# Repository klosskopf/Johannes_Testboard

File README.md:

# ECP5_Breakout_with_DDR2  
A LFE5U-25F68G256CFDG Breakout board with DDR2 x8 and Spi-Flash  
  
This breakout board is meant to be capable of running Linux (No idea if thats the case)  
  
### It features:  
-LFE55U-25F68G256CFDG FPGA  
-E1109AFGB 1Gbit DDR2 (desoldered from a DIMM)  
-W25Q128FV 128Mbit QSPI-Flash  
-44 GPIO Pins  

### Programming
I usually use a Altera-USB blaster as jtag cable.
That works pretty good, but I have to ignore a status bit during programmin
The programming-pinout on the board is:
|1|2||3|4|5|6|7|8|9|10|
|-|-|-|-|-|-|-|-|-|-|-|
|VIN(5V)|GND||VCC|TDO|TDI|NC|NC|TMS|GND|TCK|

This is the correct pinout for the USB ispDOWNLOAD Cable H-USBN-2A

Initial programming is done via JTAG (In my case ispDOWNLOAD Cable HW-USBN-2A))  
In future a "bootloader" should be built, to configure the Flash via serial  
  
**Do not expect this to be optimal.**  
**Do not expect this to be halfway decent.**  
**Do not expect this to work.**  
**Do not use this, but on your own risc**

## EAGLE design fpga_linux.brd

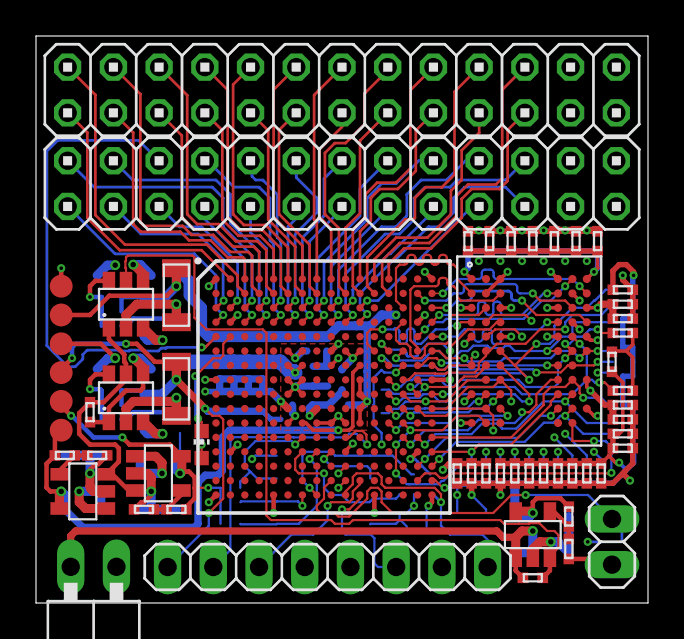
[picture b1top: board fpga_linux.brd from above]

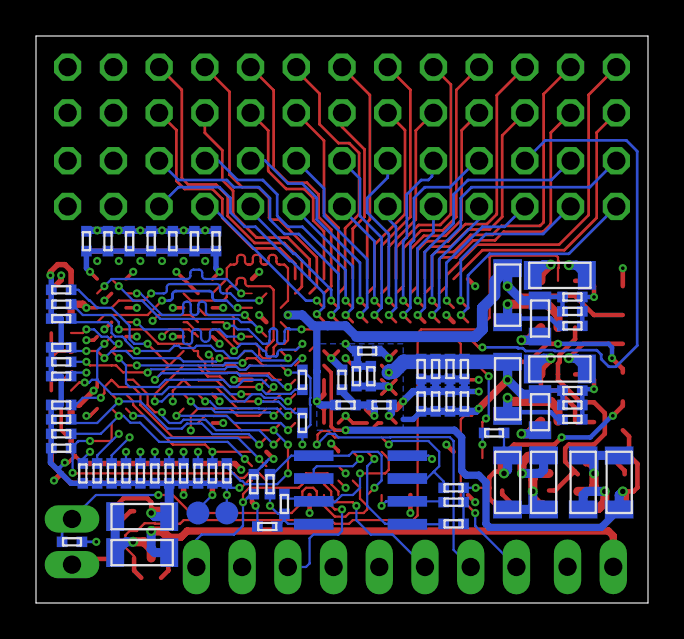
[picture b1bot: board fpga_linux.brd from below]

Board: 4 copper layers, 34.0 x 31.5 mm, 131 parts (74 on the bottom side), 110 nets.

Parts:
C1, C2, C3, C4, C5, C6, C7, C8, C9, C10, C11, C12, C13, C14, C15, C16, C17, C18, C19, C20, C21, C22, C23, C24, C25, C26, C27, C28, C29, C30, C31, C32, C33, C34, C35, C36, C37, C38, C39, C40, C41, C42, C43, C49, C50, C53, C54, C55: 0402
IC1: E1109AFGB; DDR2X8
IC2: LFE5U-25F68G256CFDG; BGA256C80P16X16_1400X1400X170
JP1: 1X08
JP2: 1X02
JP3, JP4: 2X13
LED1: CHIP-LED0603
POW:C1, POW:C2, POW:C4, POW:C5, POW:C7, POW:C8, POW:C9, POW:C11, POW:C12, POW:C13, POW:C14, POW:C15: 10u; 1206
POW:C3, POW:C10: 22p; 0402
POW:IC1, POW:IC4, POW:IC5: AP2127; SOT23-5
POW:IC2, POW:IC3: FP6373A; SOT23-6
POW:JP1: 1X02/90
POW:L1, POW:L2: 1u5; 0805
POW:R1: 56k2; 0402
POW:R2: 2k2; 0402
POW:R3, POW:R5, POW:R6: 18k; 0402
POW:R4: 38k3; 0402
POW:R7, POW:R9: 10k; 0402
POW:R10: 83k33; 0402
POW:R11, POW:R13: 100k; 0402
POW:R12: 200k; 0402
POW:TP1, POW:TP2, POW:TP3, POW:TP4, POW:TP5, POW:TP6, POW:TP7, POW:TP8: TPB1,27; B1,27
R1, R2, R8, R9, R10, R11, R12, R13, R14, R15, R16, R17, R18, R19, R20, R21, R22, R23, R24, R25, R26, R27, R28, R29, R30, R31, R32, R33: 0402
R3: 4k7; 0402
R4, R5, R6, R7: 10k; 0402
U$1: W25Q64FCSOIC8; SOIC8

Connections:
1V8: C3.2, C4.2, C5.2, C6.2, C7.2, C8.2, C9.2, C10.2, C11.2, C12.2, C13.2, C14.2, C15.2, C16.2, C17.2, C18.2, C19.2, C20.2, C21.2, C22.2, C23.2, C43.2, IC1.A1, IC1.A9, IC1.C1, IC1.C3, IC1.C7, IC1.C9, IC1.E1, IC1.E9, IC1.H9, IC1.L1, IC2.H11, IC2.J11, IC2.K11, IC2.L11, POW:C10.1, POW:C11.1, POW:C12.1, POW:L2.2, POW:R12.1, POW:TP2.TP
+3V3: C1.1, C49.2, C50.2, C53.2, C54.2, C55.2, IC2.F6, IC2.F7, IC2.F10, IC2.F11, IC2.H6, IC2.H7, IC2.J6, IC2.J7, IC2.L6, IC2.P10, JP3.25, JP3.26, JP4.25, JP4.26, POW:C1.1, POW:IC4.5, POW:R1.1, POW:TP5.TP, R3.1, R4.1, R5.1, R6.1, R7.1, R31.2, R33.1, U$1.8
FLASH_CLK: IC2.N9, U$1.6
FLASH_CS_N: IC2.N8, R3.2, U$1.1
FLASH_IO0: IC2.T8, R4.2, U$1.5
FLASH_IO1: IC2.T7, R5.2, U$1.2
FLASH_IO2: IC2.M7, R6.2, U$1.3
FLASH_IO3: IC2.N7, R7.2, U$1.7
GND: C1.2, C3.1, C4.1, C5.1, C6.1, C7.1, C8.1, C9.1, C10.1, C11.1, C12.1, C13.1, C14.1, C15.1, C16.1, C17.1, C18.1, C19.1, C20.1, C21.1, C22.1, C23.1, C24.1, C25.1, C26.1, C27.1, C28.1, C29.1, C30.1, C31.1, C32.1, C33.1, C34.1, C35.1, C36.1, C37.1, C38.1, C39.1, C40.1, C41.1, C42.1, C43.1, C49.1, C50.1, C53.1, C54.1, C55.1, IC1.A3, IC1.A7, IC1.B2, IC1.B8, IC1.D2, IC1.D8, IC1.E3, IC1.E7, IC1.J1, IC1.K9, IC2.A1, IC2.A16, IC2.D2, IC2.D15, IC2.F8, IC2.F9, IC2.G8, IC2.G10, IC2.H1, IC2.H8, IC2.H9, IC2.H10, IC2.H16, IC2.J8, IC2.J9, IC2.J10, IC2.K6, IC2.K7, IC2.K8, IC2.K9, IC2.K10, IC2.N2, IC2.N10, IC2.N15, IC2.R10, IC2.T1, IC2.T5, IC2.T12, IC2.T16, JP1.2, JP2.1, JP3.23, JP3.24, JP4.23, JP4.24, POW:C1.2, POW:C2.2, POW:C4.2, POW:C5.2, POW:C7.2, POW:C8.2, POW:C9.2, POW:C11.2, POW:C12.2, POW:C13.2, POW:C14.2, POW:C15.2, POW:IC1.2, POW:IC2.2, POW:IC3.2, POW:IC4.2, POW:IC5.2, POW:JP1.1, POW:R3.2, POW:R5.2, POW:R6.2, POW:R11.2, POW:R13.2, POW:TP6.TP, POW:TP8.TP, R32.1, U$1.4
LED_N: IC2.E2, LED1.C
unnamed: C2.2, R1.1, R30.1
unnamed: LED1.A, R33.2
PIN1: IC2.B3, JP4.2
PIN2: IC2.B4, JP4.4
PIN3: IC2.B5, JP4.6
PIN4: IC2.B6, JP4.8
PIN5: IC2.A6, JP4.10
PIN6: IC2.A7, JP4.12
PIN7: IC2.A8, JP4.14
PIN8: IC2.B10, JP4.16
PIN9: IC2.B11, JP4.18
PIN10: IC2.B12, JP4.20
PIN11: IC2.B13, JP4.22
PIN12: IC2.A2, JP4.1
PIN13: IC2.A3, JP4.3
PIN14: IC2.A4, JP4.5
PIN15: IC2.A5, JP4.7
PIN16: IC2.B7, JP4.9
PIN17: IC2.B8, JP4.11
PIN18: IC2.A9, JP4.13
PIN19: IC2.A10, JP4.15
PIN20: IC2.A11, JP4.17
PIN21: IC2.A12, JP4.19
PIN22: IC2.A13, JP4.21
PIN23: IC2.C3, JP3.2
PIN24: IC2.D4, JP3.4
PIN25: IC2.E1, JP3.6
PIN26: IC2.D5, JP3.8
PIN27: IC2.C5, JP3.10
PIN28: IC2.C6, JP3.12
PIN29: IC2.D7, JP3.14
PIN30: IC2.D8, JP3.16
PIN31: IC2.C8, JP3.18
PIN32: IC2.C9, JP3.20
PIN33: IC2.D10, JP3.22
PIN34: IC2.D1, JP3.1
PIN35: IC2.C1, JP3.3
PIN36: IC2.C2, JP3.5
PIN37: IC2.D3, JP3.7
PIN38: IC2.C4, JP3.9
PIN39: IC2.D6, JP3.11
PIN40: IC2.C7, JP3.13
PIN41: IC2.D9, JP3.15
PIN42: IC2.C10, JP3.17
PIN43: IC2.C11, JP3.19
PIN44: IC2.D11, JP3.21
POW:1V1UP: POW:IC1.3, POW:IC2.5, POW:IC3.1, POW:IC4.3, POW:R9.2
POW:1V8UP: POW:IC3.5, POW:IC5.3, POW:R7.2
POW:N$1: POW:IC1.4, POW:R4.2, POW:R5.1
POW:N$2: POW:IC3.3, POW:L2.1
POW:N$3: POW:C3.2, POW:IC2.6, POW:R10.2, POW:R11.1
POW:N$4: POW:IC2.3, POW:L1.1
POW:N$5: POW:IC4.4, POW:R1.2, POW:R3.1
POW:N$6: POW:IC5.4, POW:R2.2, POW:R6.1
POW:N$7: POW:C10.2, POW:IC3.6, POW:R12.2, POW:R13.1
RAM_A0: IC1.H8, IC2.M16, R23.2
RAM_A1: IC1.H3, IC2.K16, R22.2
RAM_A2: IC1.H7, IC2.M14, R21.2
RAM_A3: IC1.J2, IC2.K13, R20.2
RAM_A4: IC1.J8, IC2.M15, R19.2
RAM_A5: IC1.J3, IC2.K14, R18.2
RAM_A6: IC1.J7, IC2.N16, R17.2
RAM_A7: IC1.K2, IC2.K15, R16.2
RAM_A8: IC1.K8, IC2.P16, R15.2
RAM_A9: IC1.K3, IC2.L13, R14.2
RAM_A10: IC1.H2, IC2.J14, R13.2
RAM_A11: IC1.K7, IC2.P15, R12.2
RAM_A12: IC1.L2, IC2.L14, R11.2
RAM_A13: IC1.L8, IC2.R15, R10.2
RAM_BA0: IC1.G2, IC2.H15, R9.2
RAM_BA1: IC1.G3, IC2.J13, R8.2
RAM_BA2: IC1.G1, IC2.G16, R2.2
RAM_CAS_N: IC1.G7, IC2.G15, R26.2
RAM_CKE: IC1.F2, IC2.H14, R28.2
RAM_CK_N: IC1.F8, IC2.J15, R1.2
RAM_CK_P: IC1.E8, IC2.J16, R30.2
RAM_CS_N: IC1.G8, IC2.G13, R24.2
RAM_D0: IC1.C8, IC2.B15
RAM_D1: IC1.C2, IC2.D14
RAM_D2: IC1.D7, IC2.E16
RAM_D3: IC1.D3, IC2.F13
RAM_D4: IC1.D1, IC2.F12
RAM_D5: IC1.D9, IC2.C16
RAM_D6: IC1.B1, IC2.C14
RAM_D7: IC1.B9, IC2.B16
RAM_DM: IC1.B3, IC2.F15
RAM_DQS_N: IC1.A8, IC2.E15
RAM_DQS_P: IC1.B7, IC2.D16
RAM_ODT: IC1.F9, IC2.F16, R29.2
RAM_RAS_N: IC1.F7, IC2.F14, R25.2
RAM_WE_N: IC1.F3, IC2.H13, R27.2
RESET_N: IC2.R9, JP2.2, R31.1
TCK: IC2.T10, JP1.1, R32.2
TDI: IC2.R11, JP1.6
TDO: IC2.M10, JP1.7
TMS: IC2.T11, JP1.3
VCC: C30.2, C31.2, C37.2, C38.2, C39.2, C40.2, C41.2, C42.2, IC2.G6, IC2.G7, IC2.G9, IC2.L8, IC2.L9, IC2.L10, JP1.8, POW:C3.1, POW:C7.1, POW:C8.1, POW:L1.2, POW:R10.1, POW:TP3.TP
VCCAUX: IC2.G11, IC2.L7, POW:C13.1, POW:IC1.5, POW:R4.1, POW:TP4.TP
VIN: POW:C2.1, POW:C5.1, POW:C9.1, POW:C14.1, POW:C15.1, POW:IC1.1, POW:IC2.1, POW:IC2.4, POW:IC3.4, POW:IC4.1, POW:IC5.1, POW:JP1.2, POW:R7.1, POW:R9.1, POW:TP1.TP
VTT: C2.1, C24.2, C25.2, C26.2, C27.2, C28.2, C29.2, C32.2, C33.2, C34.2, C35.2, C36.2, IC1.E2, IC2.G14, IC2.R16, POW:C4.1, POW:IC5.5, POW:R2.1, POW:TP7.TP, R2.1, R8.1, R9.1, R10.1, R11.1, R12.1, R13.1, R14.1, R15.1, R16.1, R17.1, R18.1, R19.1, R20.1, R21.1, R22.1, R23.1, R24.1, R25.1, R26.1, R27.1, R28.1, R29.1

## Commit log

2020-09-29 Increased polygon isolation
2020-09-29 Switched from vector font
2020-09-29 adjusted DRAM model
2020-09-30 Added gregs recommendations (pullup/down on grogramn/tck, usrled)
2020-12-04 Create LICENSE
2021-04-01 final commit
